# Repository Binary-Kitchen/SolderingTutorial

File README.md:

# Soldering Tutorial

This repository contains all files for our soldering kits and courses. Please feel free to download and use everything you need.

We've tried to collect and create tutorials with different difficulties and are offering SMD and DIP soldering kits.

For an overview of all kits with manuals and interactive pcb views go to: https://binary-kitchen.github.io/SolderingTutorial

### Linking directly to a kit

Every kit on the overview page has its own anchor, so you can link straight to its picture:
`https://binary-kitchen.github.io/SolderingTutorial/#Capybara` opens the page scrolled to the Capybara card and highlights it.
Clicking the small link icon on a card copies that deep link to your clipboard.

The overview page is generated from the project folders — `make landing_page`, i.e. `python build_landingpage.py`.
Every folder that contains a card image at `manual/images/thumbnail.{jpg,jpeg,png,gif,webp}` shows up automatically,
so a new kit only needs such a thumbnail to appear on the page.

If you want to buy soldering Kits you can find some here: [shop.blinkyparts.com](https://shop.blinkyparts.com)

We have tips how to organise a soldering workshop in the field and how to further decorate the kits: [Wiki: Festival Setup](https://github.com/Binary-Kitchen/SolderingTutorial/wiki/Festival-Setup)

## Soldering Kits

### [50 Ohm Dummy Load](50ohmDummyLoad/)

A simple Dummy Load for 50 Ohm made for every amateur radio operator.

- Difficulty: **§/5**

### [Atari Punk Console - STEAM Edition](AtariPunkConsoleSTEAM/)

One of the simplestes Synthesizers you can build. Only two NE555 make super cool sounds!

- Difficulty: **1/5**

### [ATX Breakout Board](ATXBreakoutBoardSMD/)

Handy Breakout Board to get all the important voltages from a standard ATX power supply.

- Difficulty: **4/5**

### [Al Hacka Alpaka](AlHackaAlpaka/)

Easy soldering kit in homage to Jugend hackt and its mascot.

### [Arrow SMD](ArrowSMD/)

Small soldering kit with an arrow on it from https://wiki.blinkenarea.org/index.php/AntiKippenLights-Mini.

- Difficulty: **4/5**

### [Axolotl Badge](AxolotlBadge/)

Easy RGB soldering kit with the best Axolotl!

- Difficulty: **2/5**

### [BleepBot](BleepBot/)

A talking robot!

- Difficulty: **2/5**

### [Blinkenrocket Mini](BlinkenrocketMini/)

A very simple soldering kit and a very intuitive way to program your own led matrix. Super fun blinkenrocket!

- Difficulty: **2/5**

### [BlinkyTree](BlinkyTree/)

The BlinkyTree is a soldering kit for a fantastic soldering Christmas tree. The great feature: By blowing on the tree, you can play different songs. A wonderful soldering kit for the Christmas season.

- Difficulty: **2/5**

### [Pooping Cat](PoopingCat/)

Can you please turn around? If you stare, the cat will stare back in all colours of the rainbow due to RGB-LEDs on the back. The soldering kit is very simple and easy to assemble.

- Difficulty: **2/5**

### [Cube DIP](CubeDIP/)

Simple LED cube consisting of 27 RGB LEDs in a 3x3x3 configuration. No programming needed.

- Difficulty: **3/5**

### [Daisy RGB](Daisy_RGB/)

This 3D construction kit allows you to solder a personalized daisy with a large RGB LED in the center, with colors adjustable using variable resistors and overall brightness and individual colors adjustable via slide switches.

- Difficulty: **2/5**

### [Dice DIP](DiceDIP/)

Electronic dice which uses button bouncing and timing for randomness.

- Difficulty: **3/5**

### [Dice Micro Controller DIP](DiceMcDIP/)

Dice with micro controller. Electronic dice which uses C random generator.

- Difficulty: **2/5**

### [Dino](Dino/)

This rainbow dinosaur will brighten up your life. The spikes are glowing in all colours of the rainbow due to RGB-LEDs on the back. The soldering kit is very simple and easy to assemble.

- Difficulty: **2/5**

### [Draussenfuchs Antenna](DraussenfuchsAntenne/)

A soldering kit for a simple 433MHz Yagi antenna designed for the draussenfuchs.de fox hunting game.

- Difficulty: **2/5**

### [Draussenfuchs Sender](DraussenfuchsSender/)

A soldering kit for a 433MHz fox sender for the draussenfuchs.de fox hunting game.

- Difficulty: **2/5**

### [Elefant](Elefant/)

Everyone knows the great elephant from the “Sendung mit der Maus” and, as always, he has a good idea. An LED in the trunk that lights up in RGB colors.

- Difficulty: **2/5**

### [Ermer Beeper DIP](ErmerBeeperDIP/)

The Ermer Beeper is a very neat continuity tester or beeper.

- Difficulty: **2/5**

### [Heartbeat](HeartbeatTHT/)

Small soldering kit with an heart and a beating led in the middle.

- Difficulty: **2/5**

### [Heart DIP](HeartDIP/)

Small soldering kit with an heart on from https://wiki.blinkenarea.org/index.php/AntiKippenLights-Atmel

- Difficulty: **2/5**

### [Heart SMD](HeartSMD/)

Small soldering kit with an heart on it from https://wiki.blinkenarea.org/index.php/AKL-Mini

- Difficulty: **4/5**

### [Humo - Solder-Fume Exctractor](Humo/)

This simple solder fume extractor just needs a PC fan and a solder fume filter. If you add some goggly eyes the fume extractor has a pretty nice smiling face. It is optimised for laser cut parts.

- Difficulty: **2/5**

### [I Can Solder DIP](ICanSolderDIP/)

Very easy soldering kit with three LEDs. Can be used as pin button.

- Difficulty: **1/5**

### [Katie The Cat](KatieTheCat/)

A wonderful and easy soldering Kit with two different eye-colours.

- Difficulty: **2/5**

### [Kitchen Head SMD](KitchenHeadSMD/)

Small soldering kit using SMD components with the kitchen head on it.

- Difficulty: **4/5**

### [LEDSchmuck](LEDSchmuck/)

The LED jewelry kit allows you to easily and quickly assemble earrings or pendants with RGB LEDs. It's a creative kit for making great individual jewelry pieces.

- Difficulty: **2/5**

### [LEDWolf](LEDWolf/)

This great LED wolf is a good way to start tinkering if you don't have a soldering iron with you at the moment. All you need is a little glue and a small Phillips screwdriver to assemble this great wolf.

- Difficulty: **1/5**

### [Maus](Maus/)

An easy hot wire soldering kit with the Sendung mit der Maus.

### [Moon Cat](MoonCat/)

Excuse me? What are you staring at? This wonderful kit is very simple in terms of circuitry, but the result is simply hilarious.

- Difficulty: **2/5**

### [Motörbörd](MotoerBoerd/)

Chirp chirp chirp, chirp chirp! The Motörbörd is a creative soldering kit that you can use to build your own little bird call generator. It is not powered by batteries, but by a small motor that generates electrical energy when turned like a dynamo.

- Difficulty: **2/5**

### [Mushroom Rocket](https://github.com/ventilator/soldering-mushroom-rocket/tree/main)

A fusion between a rocket and a mushroom

- Difficulty: **2/5**

### [NE555 Heart THT](NE555HeartTHT/)

A wonderful Heart with SMD LEDs. You can choose between full on, follow-LEDs and even can influence the speed of your LEDs.

- Difficulty: **3/5**

### [NE555 Heart SMD](NE555HeartSMD/)

A wonderful Heart with SMD LEDs. You can choose between full on, follow-LEDs and even can influence the speed of your LEDs.

- Difficulty: **4/5**

### [Nibble++](NibblePlusPlusSMD/)

A simple PCB to test your SMD hand-soldering skills. Going down to sand grain sized 01005 SMD parts, this button is a challenge for experienced "soldiers" and those who want to become one.

- Difficulty: **6/5**

### Nibble Peg DIP

#### [Nibble Peg DIP](NibblePegDIP/)

Very easy soldering Kit using simple Tools and nearly no soldering knowledge is needed.

- Difficulty: **1/5**

#### [Nibble Peg DIP with On/Off Switch](NibblePegDIPSwitch/)

Easy soldering Kit using simple Tools and nearly no soldering knowledge is needed.

- Difficulty: **2/5**

### [Nose Dog](NoseDog/)

Easy soldering Kit using simple Tools and nearly no soldering knowledge is needed.

- Difficulty: **2/5**

### [OpenDTU Breakout Board](OpenDTU_Breakout/)

A board to get information from your solar power panels with an Hoymiles inverter.

- Difficulty: **2/5**

### [Owl Thief THT](OwlThiefDIP/)

A simple joule thief circuit on the back of an owl. If you solder everything right, you can empty old batteries and make the eyes glow orange.

- Difficulty: **2/5**

### [Pinecil Case](Pinecil_Case/)

A perfect 3D-printed rugged case for your pinecil, extra tips and usb-c cable.

- Difficulty: **1/5**

### [Push-It DIP](PushItDIP/)

Simon Says clone with (optional) multiplayer mode

- Difficulty: **2/5**

### [Rainbow Butterfly](RainbowButterfly/)

A wonderful rainbow Butterfly. The wings are enlighted by RGB-LEDs from the back of the PCB. The soldering kit is very simple and easy to assemble.

- Difficulty: **2/5**

### [Rainbow Unicorn 1](RainbowUnicorn01/)

This unicorn will brighten up your life. The hair is glowing in all colours of the rainbow due to RGB-LEDs on the back. The soldering kit is very simple and easy to assemble.

- Difficulty: **2/5**

### [Ring Light SMD](RingLightSMD/)

A simple SMD learning kit where a light chases around a circle.

- Difficulty: **4/5**

### [Robo Robin](RoboRobin/)

Light up this super easy Robot. It has RGB-LEDs as eyes.

- Difficulty: **1/5**

### [Rainbow Rocket](RocketBadge/)

Fly to the moon with this RGB rocket badge.

- Difficulty: **2/5**

### [Saw-Tooth Organ DIP](SawToothOrganDIP/)

Some Transistors creating a saw tooth wave enabling a very simple organ which you can play like a piano with a stylus.

- Difficulty: **2/5**

### [Shitty Robot](ShittyRobots/)

A very easy circuit to power a little robot with a vibration motor.

- Difficulty: **1/5**

### [SmartLED](SmartLED/)

Create a wonderful smart LED-Lamp you can control with you Smartphone.

- Difficulty: **4/5**

### [Smartphone Robot](SmartphoneRobot/)

A robot made out of an old smartphone. You can controll it by turning light on and off.

- Difficulty: **2/5**

### [SMD Cat](SMDCat/)

A Cat in a box easy SMD kit. Bright glowing LED-eyes are watching every step! With this soldering kit it is super easy to learn SMD soldering.

- Difficulty: **3/5**

### [Solarpunk Synthesizer](SolarpunkSynth/)

A very simple solarpunk Synthesizer based on a simple Schmitt Trigger. Create crazy sounds with this simple soldering kit.

- Difficulty: **2/5**

### [SolderBox](SolderBox/)

We have designed a soldering box for you that is extra small but still contains everything you need. The box offers space for a complete soldering working place and is still so small that four of the boxes fit into a small Euro box.

- Difficulty: **1/5**

### [SpaceEggs](SpaceEggs/)

The **Space Egg** is a fun and beginner-friendly **soldering kit** combined with **3D-printed components**. It features an interactive mechanism where turning the egg

- Difficulty: **2/5**

### [WeevilEye](WeevilEye/)

The kit is a very easy kit with push-through parts, which is explicitly aimed at beginners. Once assembled, the red LED “eyes” light up brighter or dimmer depending on how much light falls on the photo sensor.

- Difficulty: **2/5**

## License

This work is licensed under different licenses. Please see subfolders for details and LICENSE.md file in the top level directory for all used license files.

## Copyright and Authorship

Please consider README.md in sub-folders for the Copyright and Authorship of the specific project.

## Authors

Boards:

- Arne Rossius [arne@blinkenarea.org](mailto:arne@blinkenarea.org)
- Thomas Basler [noby@binary-kitchen.de](mailto:noby@binary-kitchen.de)
- Francesco Truzzi <http://truzzi.me>
- Timo Schindler <https://www.timoschindler.de>
- Thomas Schmid

TeX-Code:

- Marei Peischl [marei@binary-kitchen.de](mailto:marei@binary-kitchen.de) <https://github.com/TeXhackse>

Comic:

- Mitch Altmann <http://cornfieldelectronics.com>
- Jeff Keyzer <http://mightyohm.com/blog/>
- Andie Nordgren [andie.nordgren@gmail.com](mailto:andie.nordgren@gmail.com)

Manuals:

- Michael Pajewski
- Marei Peischl [marei@binary-kitchen.de](mailto:marei@binary-kitchen.de) <https://github.com/TeXhackse>
- Timo Schindler <https://www.timoschindler.de>
- Hannes <https://github.com/misamura>
- Mario Langhammer <https://github.com/Mallo321123>

Note: This list of authors can be incomplete. Please also consider the README.md in the sub-folders for authorship.

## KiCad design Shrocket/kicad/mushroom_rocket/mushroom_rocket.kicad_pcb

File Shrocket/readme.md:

# Mushroom Rocket

Easy soldering kit for a music festival

Video: video/switch_on_front_and_back_side.webm

# Made with

* Affinity Designer
* [Gingerbread](https://gingerbread.wntr.dev/index.html)
* KiCad
    * Blinkyparts custom footprint library (submodule) [https://codeberg.org/blinkyparts/blinkyparts.pretty](https://codeberg.org/blinkyparts/blinkyparts.pretty)

# Soldering tutorial

Prepare the parts

Add solder to the long pad of the bottom LED

Bend the legs of one LED to look like this

Solder one LED at the bottom. Solder the long leg to the long pad with the + sign

Should look like this

Add solder to the long pads of the 3 top LEDs

Solder the remaining 3 LEDs to the 3 pads on top.

Should look like this

Snip the excess legs

Should look like this

Clip the legs of the 3 top LEDs.

Bend the legs of the switch so they touch the table.

Solder one leg of the switch

Solder the other leg of the switch

Add solder to the left pad of the battery holder.

Solder the left leg of the battery holder

Finished with soldering

Add the battery. Careful: the left arms must go on top of the battery, and the longer right arms below.

It should look like this. Check again that the 2 small arms on the left side of the battery holder touch the battery from the top.

Finished with soldering

Switch it on and check if all LEDs light up.

They should switch from red to green

Add hot glue to the LEDs

Only a small drop

A bit of hot glue at the bottom LED

Finished. Now decorate the front side with glitter if you want to.

Animation
Back side

Front side

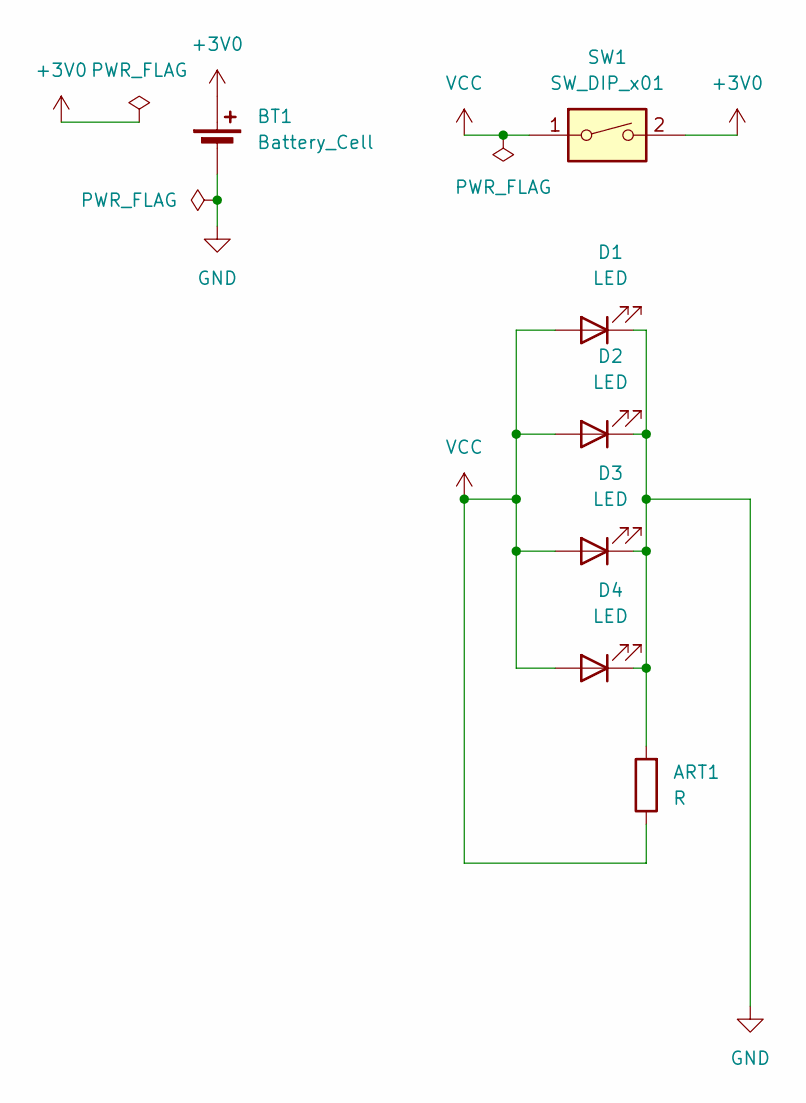
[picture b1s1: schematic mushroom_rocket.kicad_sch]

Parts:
ART1: R; Footprint_Mushroom_v0.6
BT1: Battery_Cell; BatteryHolder_Keystone_1060_1x2032_HandSoldering
D1, D2, D3, D4: LED; 5mm_SMD-Pad
SW1: SW_DIP_x01; Push_Button

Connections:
+3V0: BT1.1 (+), SW1.2
GND: ART1.2, BT1.2 (-), D1.1 (K), D2.1 (K), D3.1 (K), D4.1 (K)
VCC: ART1.1, D1.2 (A), D2.2 (A), D3.2 (A), D4.2 (A), SW1.1

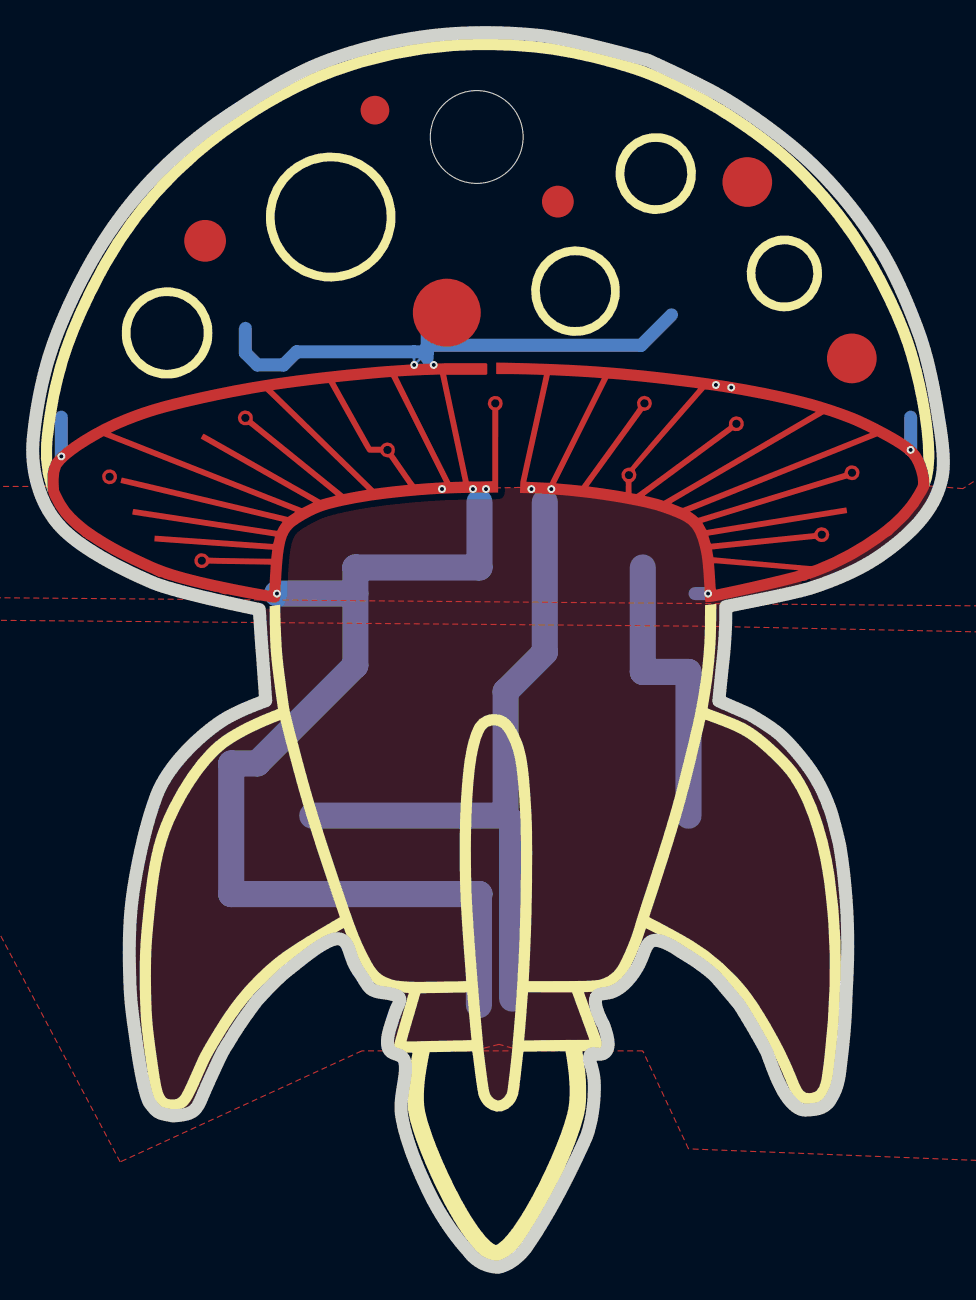
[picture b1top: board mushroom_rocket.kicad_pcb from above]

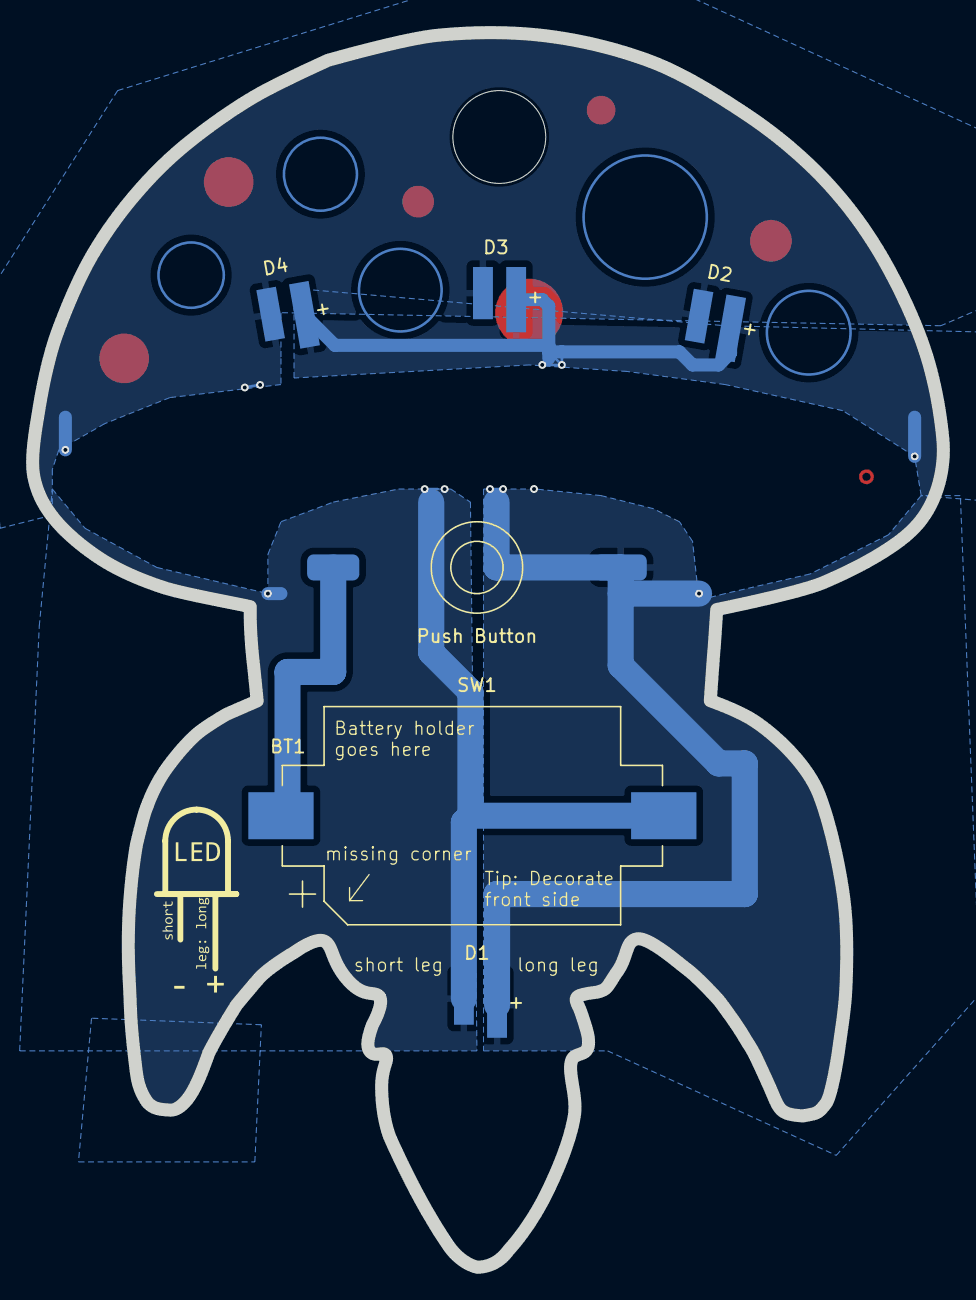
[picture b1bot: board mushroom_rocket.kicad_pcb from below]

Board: 2 copper layers, 69.7 x 94.5 mm, 7 parts (6 on the bottom side), 3 nets.

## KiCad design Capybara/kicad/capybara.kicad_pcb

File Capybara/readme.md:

# Capybara

A simple RGB LED badge

Made by Alex and Clemens, using Alex' [PCB Designer](https://alber.me/miscellaneous/tools/pcb-designer.html), which generated Gerber and KiCAD files

## Overview page

This kit is listed on the [soldering kit overview](https://binary-kitchen.github.io/SolderingTutorial/#Capybara).
The card image is `manual/images/thumbnail.jpg`, the same place every other kit keeps it.

## Interactive Schematics

[Interactive Schematics](ibom.html)

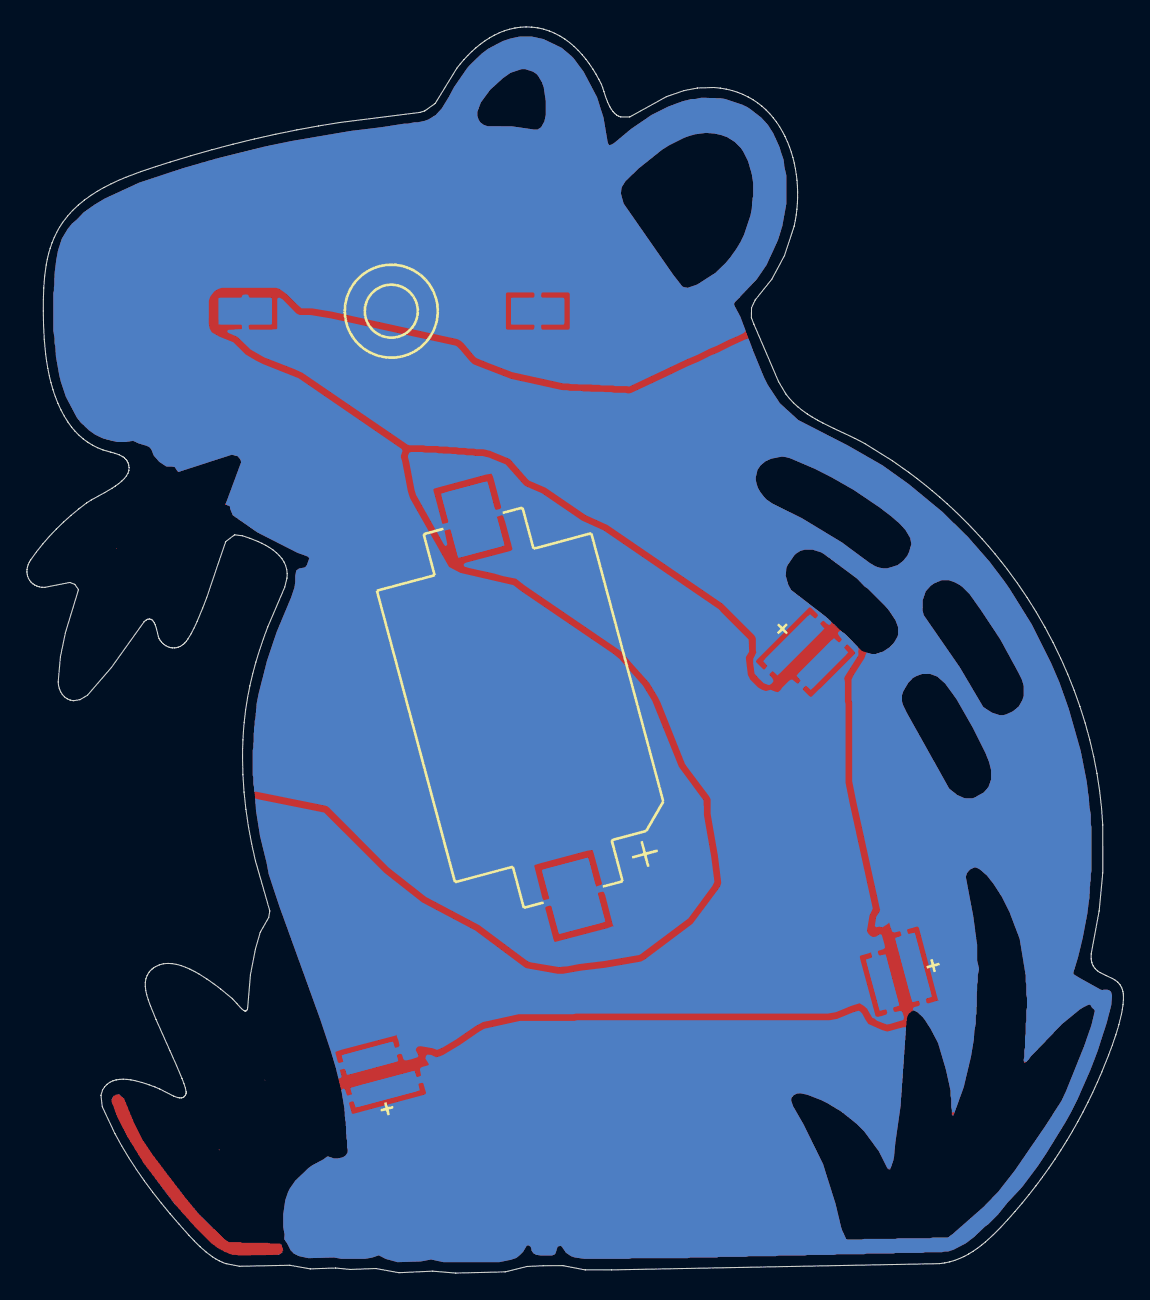
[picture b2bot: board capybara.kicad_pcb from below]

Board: 2 copper layers, 82.5 x 93.7 mm, 5 parts (5 on the bottom side), 2 nets, no tracks yet.

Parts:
BAT 1: BAT; battery
LED 1, LED 2, LED 3: LED; led
SW 1: SW; button

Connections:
GND: BAT 1.-, LED 1.K, LED 2.K, LED 3.K
VCC: LED 1.A, LED 2.A, LED 3.A

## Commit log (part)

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2018-12-04 added new picture
2018-12-04 added board layout to manual
2018-12-04 adjusted board layout size
2018-12-04 recompiled manuals with new information
2018-12-13 added duration for pdfs
2018-12-13 added duration for labels and removed board and description version
2018-12-13 added 2--4 hours duration for atx breakoutboard
2018-12-13 added 1--2 hours duration for arrow smd
2018-12-13 added 1--2 hours duration for diceDIP
2018-12-13 added 1--2 hours duration for diceMcDIP
2018-12-13 added 1--2 hours duration for HeartDIP
2018-12-13 added 1--2 hours duration for KitchenHeadSMD
2018-12-13 added 20--40 minutes duration for NibblePeg
2018-12-13 added 20--40 minutes duration for NibblePegSwitch
2018-12-13 fixed an error with too wide headlines
2019-01-04 Add French translation for NibblePegDIPSwitch tutorial
2019-02-13 added first draft of the nibble++ description
2019-02-13 added readme
2019-04-19 Update README.md
    fix typo
    update resistor values
2019-08-11 Fixed resistor value
2019-08-13 exchanged box with boxes.py-box and updated svg
2019-08-13 updated parts-list to 7 box elements
2019-08-21 changed english step-file to represent new box. Simplified steps
2019-08-23 fixed description and added new pictures. Simplified manual
2019-08-23 fixed error
2019-08-23 updated pdf
2019-08-23 fixed errors and updated version
2019-11-06 sorted by alphabetic order
2019-11-06 added manual for I Can Solder
2019-11-06 added german translation for NibblePeg-Poster
2019-11-06 added picture
2019-11-06 fixed some error
2019-11-09 added Shitty Robots project
2019-11-09 display image license in manual
2019-11-12 use images without text where possible; additional german versions for the rest
2019-11-12 creative part should be part of manual
2019-11-13 fixing error and adding picture
2019-11-15 Refine nibble peg manuals.
2019-11-15 Edit readme.
2019-12-14 minor change from zaesa
2019-12-15 PushItDIP: Added first version of README.md
2019-12-15 PushItDIP: Added schematic
2019-12-15 PushItDIP: Added first version of pre developed source
2019-12-15 PushItDIP: Added first part of the manual
2019-12-15 PushItDIP: Fixed compiler warnings
2019-12-15 PushItDIP: Fixed several compiler warnings
2019-12-15 PushItDIP: Added .editorconfig
2019-12-15 PushItDIP: Fix several compiler warnings
2019-12-15 PushItDIP: Fixed compiler warning
2019-12-15 PushItDIP: Add settings.json to .gitignore
2019-12-15 PushItDIP: Changed board version to 1.1
    Changed position of texts for the multiplayer connector
2019-12-15 PushItDIP: Added parts and image to README.md
2019-12-15 PushItDIP: Fixed initialization issue with random number generator
2019-12-15 PushItDIP: Added cam job and gerber files for JLCPCB
2019-12-15 PushItDIP: Set the right fuses using PlatformIO
2019-12-15 PushItDIP: Erase when writing fuses
2019-12-15 PushItDIP: Fixed wrong part count
2019-12-15 PushItDIP: Enable watchdog and changed pin numbers from analog to digital
2019-12-15 PushItDIP: Moved Kitchen logo to layer tStop
2019-12-15 PushItDIP: Corrected naming of 7segement display
    Its called LED7 instead of LED5
2019-12-15 PushItDIP: Renamed SP1 to SG1 within the manuals (to match schematic)
2019-12-15 PushItDIP: First version of building steps
2019-12-15 PushItDIP: Added manual to use sticky tape in final stages
2019-12-21 PushItDIP: Migrated setting of fuses from python file to platformio.ini
2019-12-21 PushItDIP: Added some delay in multiplayer gameplay
2019-12-21 PushItDIP: Added simple compilation manual
2019-12-21 PushItDIP: Added additional hint regarding capacitors
2019-12-22 PushItDIP: Changed status from Development to Complete
2019-12-22 PushItDIP: Add to main README.md
2019-12-25 New translated files for Esperanto version
2019-12-25 New translated files for Espranto version
2019-12-25 Esperanto translation
2019-12-26 Plenk taken out.
2019-12-28 Update README.md
    Andere Widerstände im Päckchen
2020-01-08 changed picture
2020-05-06 add landing page and interactive board views
    add landing page with links to manuals and interactive board views. The
    landing page is automatically generated from the filesystem structure.
    Place a tumbnail.[jpg, jpeg, png, gif] inside the images folder and
    optionaly an ibom.html at the root folder of the project to generate
    output for it. The interactive board views can be generated with the
    kicad plugin "InteractiveHTMlBom" [https://github.com/openscopeproject/InteractiveHtmlBom]
2020-05-06 add interactive board for nibble++
2020-05-07 README: update to include link to landing page
2020-09-02 fixed latex error due to deprecated functions
2020-09-20 generated new index.html
2020-09-20 deleted schematics, updated readme and created new bom
2020-12-05 added video
2020-12-05 fixed overview-index
2020-12-05 minor changes
2020-12-05 fixed colour code
2021-01-06 added english and german manual for humo
2021-02-07 resized images and created new pdf
2021-02-07 created new pdf
2021-02-16 fixed readme
2021-02-17 updated index.html
2021-02-21 fixed some errors
2021-02-21 added cat in a box
2021-03-03 resistor color reference
2021-03-03 complete resistor_color_ref
2021-03-03 rebase part reference
2021-05-04 deleted not needed file
2021-05-04 fixed a error in parts list
2021-05-27 added 4-digit resistor naming scheme to ATXBreakoutBoardSMD
2021-08-17 added new I can solder description
2021-08-19 updated interactive board for I can solder
2021-08-19 fixed some errors in the description
2021-08-19 added english translation
2021-08-19 added resistor colorcode to manual
2021-08-19 added resistor colours to the manual
2021-08-19 added english translation for arrow soldering kit. fixing #46
2021-08-20 added translation
2021-08-20 fixed typo
2021-08-31 fixed csv-error
2021-08-31 resized unicorn pictures
2021-08-31 added rainbow butterfly
2021-09-13 Updated ATX Manual fixes https://github.com/Binary-Kitchen/SolderingTutorial/issues/48
2021-10-23 added mooncat
2021-10-23 added moon cat
2021-10-23 fixed some issues
2021-10-23 added youtube link
2021-10-24 fixed url
2021-10-24 added german translation and fixed typo
2021-10-29 Added cat02
2021-10-30 make ce, weee, an rohs possible
2021-10-30 added warnings to config
2021-10-30 delted wrong file
2021-10-30 compiled new pdfs
2021-10-30 renamed file
2021-12-06 added ermer beeper to index/readme
2021-12-08 added owl thief to soldering tutorial
2022-01-28 fixed optional terminal connector
2022-03-28 changed some parts
2022-08-03 added axolotl
2022-08-03 added rocket
2022-08-03 added rocket and axo
2022-08-06 added Katie
2022-08-06 updated index
2022-08-08 deleted not needed files
2022-08-31 changed layout to better determine between interactive board and manual
2022-08-31 generated new pdf
2022-09-04 changed steps in the manual due to customer feedback
2022-09-04 added legal stuff to the labels
2022-09-16 mirrored led-description due to feedback of @davedarko
2022-10-24 README.md: fixed some mistakes
2022-10-24 more fixes for the respective READMEs
2022-10-24 added press-entry
2022-10-24 changes due to Franziskas feedback
2022-11-05 feat: added mention to the case in README
2022-11-06 inclueded nets and tracks in ibom
2022-11-06 added tracks
2022-11-25 refined description for atx breakoutboard
2022-11-27 added Dino to soldering tutorial
2022-11-27 a litte larger pictures
2022-11-27 added correct link
2022-11-27 removed unused files
2022-12-15 changed 4-ring colour code to 5-ring colour code
2023-01-14 added NE555 Heart
2023-01-14 updated readme and index
2023-02-26 added NE555 Heart DIP
2023-02-26 fixed a minor typo
2023-04-02 added openDTU Breakout Board
2023-04-05 added pinecil case
2023-04-11 fixed some errors in daisy manual
2023-04-14 fixed some errors in pinecil case
2023-04-21 added and fixed some parts
2023-04-23 fixed an minor error
2023-05-13 added display SH1106
2023-05-23 fixed wrong part
2023-06-08 added CMT variation to openDTU breakoutboard
2023-06-27 added update option in last step
2023-07-15 updated correct .bin-file
2023-07-17 fixed small bugs
2023-07-17 fixed link
2023-07-17 added ibom
2023-07-17 added configuration and generated pdf
2023-07-17 added Al Hacka Alpaca to readme
2023-07-17 generated new index with al hacka alpaca
2023-08-27 Add A5 Nibbleklammer Booklet
2023-09-01 fixed cat in a box 2
2023-09-17 added new tip for thumb screws
2023-09-26 OpenDTU_Breakout: Typo fixes in de_steps.csv
2023-11-28 moved files due to error in index-creation script
2023-11-28 added robo robin
2023-11-28 updated pdfs
2023-12-16 updated opendtu manual to 390 ohm resistors
2024-01-22 updated parts-list for ring-light
2024-02-26 updated warning page for humo-manual
2024-03-31 Make make clean work when nothing has been built yet
    Also don't delete index.html
2024-05-30 updated config and resistor values
2024-05-30 added pictures for new spool
2024-05-30 edited new board version
2024-06-04 added CE-Certificates to a special manual. temporaray needed
2024-06-11 added Ebyte CMT legacy manual
2024-07-02 Update de_steps.csv
    typos and clarifications
2024-07-02 Update en_steps.csv
    typos and clarifications
2024-11-30 updated code to be more robust
2024-11-30 added elefant and bug
2024-12-01 Added SmartLED Instructions
2024-12-02 updated index and readme
2024-12-02 removed wrong pdfs
2024-12-02 reduced Image size and difficulty Level for SmartLED
2024-12-06 fixed wrong 47 ohm resistor
2024-12-07 Update README.md
    Schreibweise von Jugend hackt aktuallisiert
2024-12-21 added bleepbot
2024-12-22 added SolderBox
2025-01-05 fixed typo in German Humo Instruction
2025-01-14 updated manual - parts were wrong
2025-01-22 changed 82ohm to 100ohm
2025-02-06 added manual for b-good heart
2025-02-11 new difficulty and minor changes
2025-02-11 added brass wool cover
2025-02-11 updated pictures and description
2025-03-13 updated buylink
2025-06-13 add Mario to Manuals
2025-06-16 add Draussenfuchs Manual
2025-06-16 add 50Ohm Dummy load instructions
2025-06-25 added solarpunk synth
2025-06-25 added some buy links
2025-06-25 added blinkenrocket
2025-07-07 added english humo manual
2025-07-18 Humo (German manual): spelling and grammar fixes
2025-07-26 added motorboerd
2025-07-26 fixed jpg to png
2025-08-20 fixed 9 to 10 wooden parts
2025-09-06 replaced wrong ibom for 50ohm dummy load. fixed #65
2025-09-14 Improve wording
2025-09-16 updated manual parts list for diceDIP
2025-09-16 updated manual for humo to add hint for plastic rip mentioned in #67
2025-09-16 deleted optional for cable in partslist humo
2025-09-22 added mouse manula
2025-09-22 updated readme and ibom
2025-09-22 updated main readme
2025-09-24 updated warnings for unicorn
2025-09-24 updated version number and licence
2025-10-01 added NE555HeartTHT b-ware
2025-10-13 updated manual to v1.4.
2025-10-18 updated qr-code and fixed url
2025-11-04 fixed error in parts list
2025-11-04 Fixed typos and a link in README
    Fixed multiple typos in the README and updated an incorrect website link.
2025-11-04 Fixed typos in README.md
    Fixed some typos in the README
2025-11-04 Fixed typos in README
    Fixed some typos in README
2025-11-04 Fix typos and descriptions in parts list
    Fixed three typos and the descriptions in the parts list.
2025-11-12 BlinkyTree_Manual v1
2025-11-18 Fix Issue with Resistor Colors, preventing the build
2025-11-24 updated blinkytree
2025-12-13 minor changes in description for humo
2025-12-20 updated manual for new speaker
2026-01-21 renamed catinabox to pooping cat
2026-01-21 updated humo parts list
2026-01-26 minor changes.
2026-02-18 added new heartbeat soldering kit
2026-02-26 fixed wrond pdf link for humo
2026-03-04 renamed cat01 to SMDCat
2026-04-05 fixed broken links
2026-05-01 Adding mushroom rocket
2026-05-01 updating mushroomrocket
2026-05-01 Add Mushroom rocket to readme
2026-05-09 Add Shrocket soldering kit manual
2026-05-09 Update landing page with shrocket
2026-05-09 reduce file size of thumbnail images
2026-05-10 adding copy of blinkyparts.pretty instead of submodule to shrocket
